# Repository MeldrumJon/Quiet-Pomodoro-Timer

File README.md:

# Visual-Timer

Shows timer progress on screen.  Flashes a bright LED when the timer expires 
instead of ringing or vibrating.  Useful for time management in quiet offices 
or libraries.

## Parts

- [16x2 Reflective LCD Character Display](https://www.mouser.com/ProductDetail/668-S16204XRGHS10B)
- ATMega328p-PU
    - With fuses set to use internal 8MHz clock (use Makefile: `make fuses`)
- [Rotary encoder with push button switch](https://www.mouser.com/ProductDetail/652-PEC11R4315KS0012)
- 2x [Bright LEDs](https://www.mouser.com/ProductDetail/78-TLHK46Q1R2)
- 10uF electrolytic capacitor
- 3x 0.1uF ceramic capacitors
- 2x 220 ohm resistors
- 10k ohm potentiometer
- Breakaway headers
- Battery holder for 3xAA or 3xAAA batteries

## Tools

- AVR ISP Programmer or [arduinoISP](https://www.arduino.cc/en/tutorial/arduinoISP)
- USB to TTY serial adapter for debugging.

## Schematic

## Setup

1. Install the AVR-GCC toolchain (and update your `PATH` variable, if necessary)
2. Connect the AVR ISP programmer pins to the ISP header on the PCB.
3. Connect the ATMega328p's TX pin to RX on the TTY serial adapter (optional)
4. Update the `program` and `fuses` recipes in the makefile to use your AVR 
ISP programmer.
5. Update the `serial` recipe in the makefile to use your USB to TTY serial 
adapter.
6. Run `make fuses` to set the fuses on the ATMega328p.
    - If the ATMega328p was previously set to use an external clock or crystal 
    oscillator, an external clock or crystal oscillator will be needed to set 
    the fuses.

## Programming

Run `make program` to program the ATMega328p.

## PCB

KiCAD files are in [the `hardware` Folder](./hardware).

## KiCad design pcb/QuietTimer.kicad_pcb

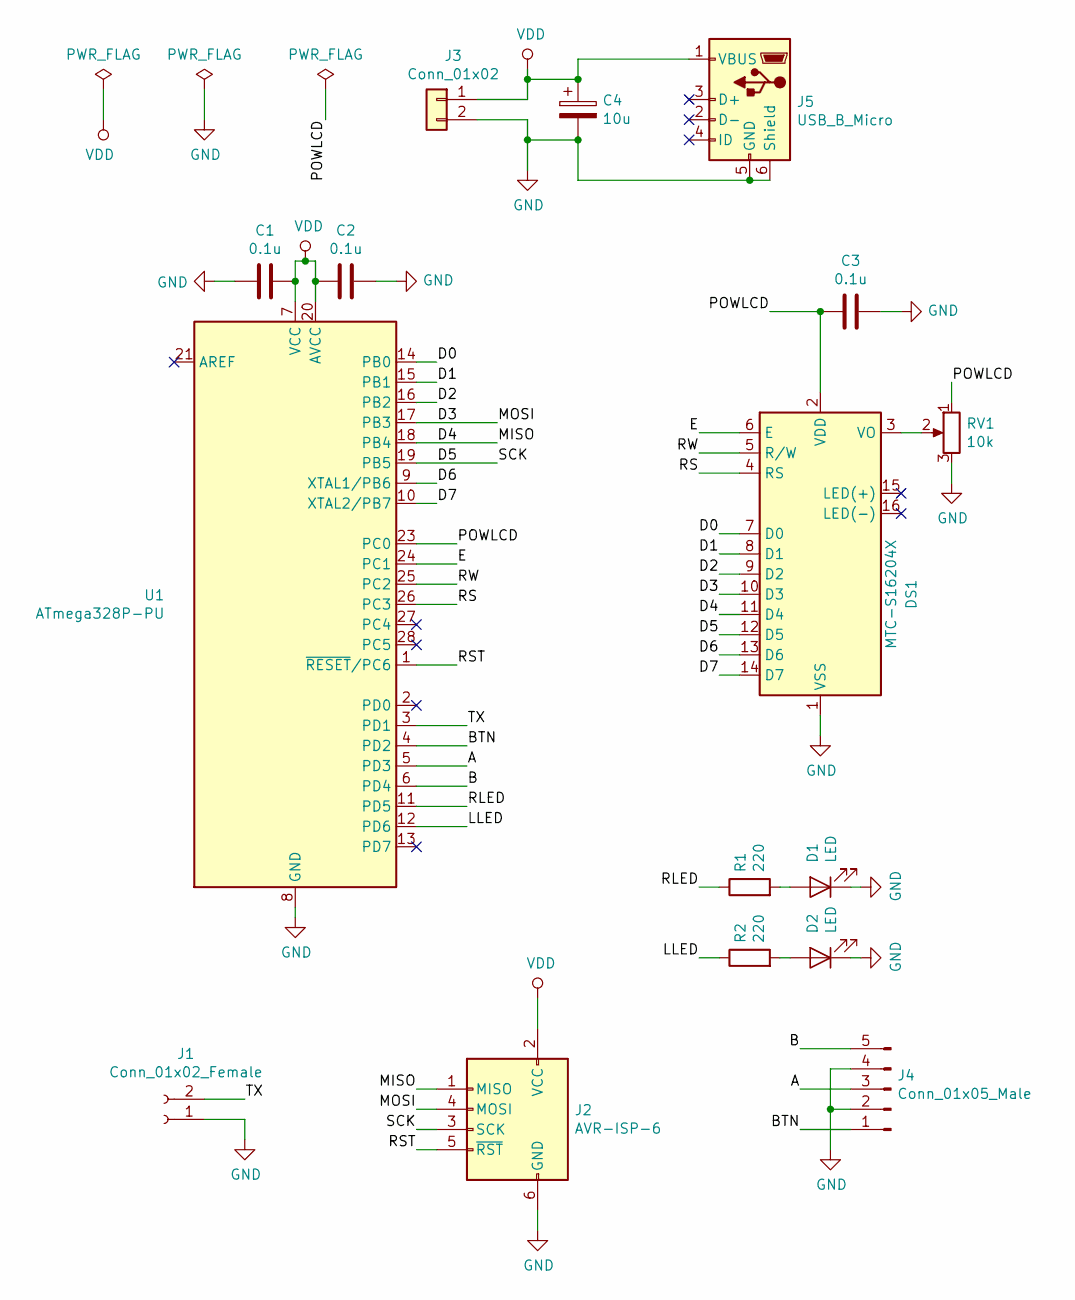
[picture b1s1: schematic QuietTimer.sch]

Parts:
C1, C2, C3: 0.1u; C_Disc_D5.0mm_W2.5mm_P2.50mm
C4: 10u; CP_Radial_D5.0mm_P2.00mm
D1, D2: LED; LED_D3.0mm
DS1: MTC-S16204X; MTC-16204X
J1: Conn_01x02_Female; PinSocket_1x02_P2.54mm_Vertical
J2: AVR-ISP-6; IDC-Header_2x03_P2.54mm_Vertical
J3: Conn_01x02; SolderWirePad_1x02_P3.81mm_Drill0.8mm
J4: Conn_01x05_Male; PinHeader_1x05_P2.54mm_Vertical
J5: USB_B_Micro; USB_Micro-B_Wuerth_614105150721_Vertical
R1, R2: 220; R_Axial_DIN0207_L6.3mm_D2.5mm_P2.54mm_Vertical
RV1: 10k; Potentiometer_Piher_PT-6-V_Vertical_Hole
U1: ATmega328P-PU; DIP-28_W7.62mm

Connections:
/A: J4.3, U1.5 (PD3)
/B: J4.5, U1.6 (PD4)
/BTN: J4.1, U1.4 (PD2)
/D0: DS1.7 (D0), U1.14 (PB0)
/D1: DS1.8 (D1), U1.15 (PB1)
/D2: DS1.9 (D2), U1.16 (PB2)
/D3: DS1.10 (D3), J2.4 (MOSI), U1.17 (PB3)
/D4: DS1.11 (D4), J2.1 (MISO), U1.18 (PB4)
/D5: DS1.12 (D5), J2.3 (SCK), U1.19 (PB5)
/D6: DS1.13 (D6), U1.9 (XTAL1/PB6)
/D7: DS1.14 (D7), U1.10 (XTAL2/PB7)
/E: DS1.6 (E), U1.24 (PC1)
/LLED: R2.1, U1.12 (PD6)
/POWLCD: C3.2, DS1.2 (VDD), RV1.1, U1.23 (PC0)
/RLED: R1.1, U1.11 (PD5)
/RS: DS1.4 (RS), U1.26 (PC3)
/RST: J2.5 (~RST), U1.1 (~RESET~/PC6)
/RW: DS1.5 (R/W), U1.25 (PC2)
/TX: J1.2, U1.3 (PD1)
GND: C1.2, C2.1, C3.1, C4.2, D1.1 (K), D2.1 (K), DS1.1 (VSS), J1.1, J2.6 (GND), J3.2, J4.2, J4.4, J5.5 (GND), J5.6 (Shield), RV1.3, U1.8 (GND), U1.22 (GND)
unnamed: D1.2 (A), R1.2
unnamed: D2.2 (A), R2.2
unnamed: DS1.3 (VO), RV1.2
VDD: C1.1, C2.2, C4.1, J2.2 (VCC), J3.1, J5.1 (VBUS), U1.7 (VCC), U1.20 (AVCC)

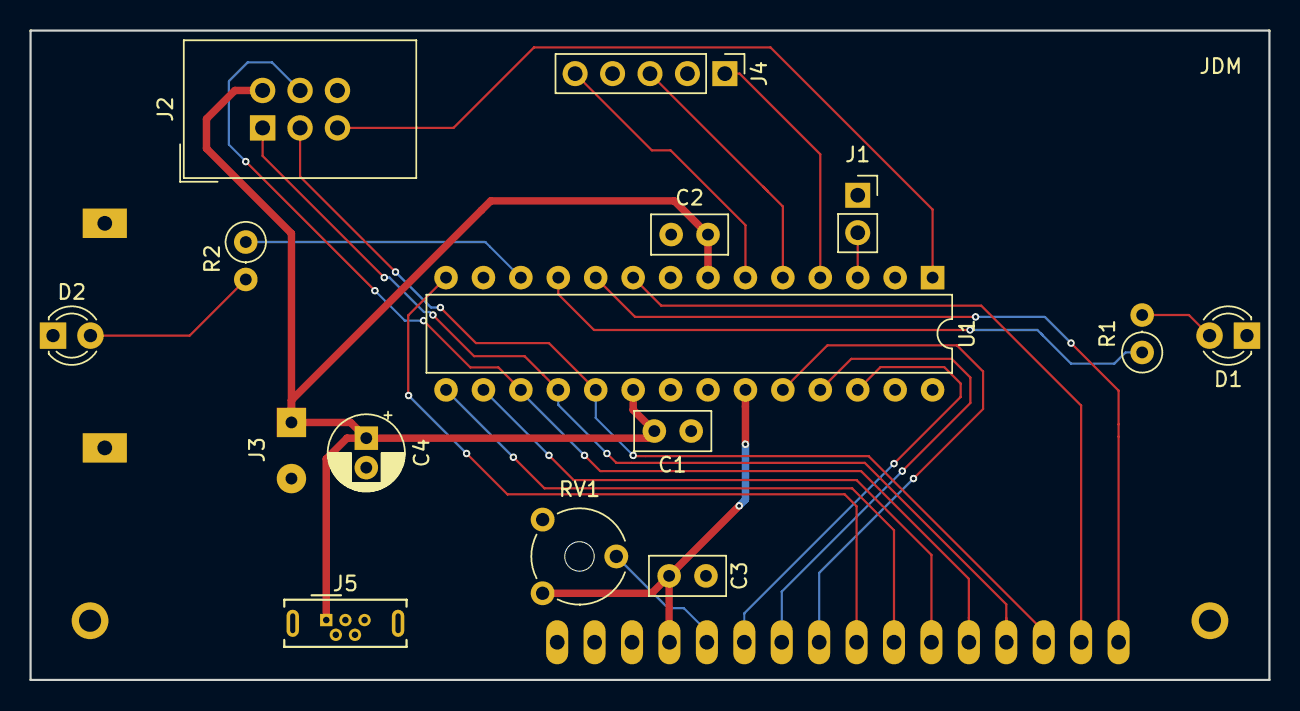
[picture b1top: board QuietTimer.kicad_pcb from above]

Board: 2 copper layers, 84.1 x 44.1 mm, 16 parts (1 on the bottom side), 24 nets.

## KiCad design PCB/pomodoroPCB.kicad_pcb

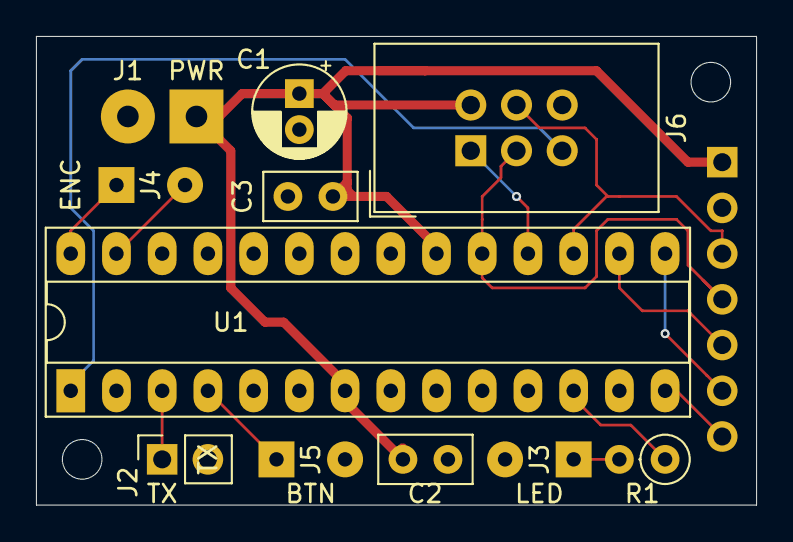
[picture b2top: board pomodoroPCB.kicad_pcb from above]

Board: 2 copper layers, 40.0 x 26.0 mm, 12 parts (1 on the bottom side), 15 nets.

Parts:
C1: 10u; CP_Radial_D5.0mm_P2.00mm
C2, C3: 0.1u; C_Disc_D5.0mm_W2.5mm_P2.50mm
J1: Conn_01x02; SolderWirePad_1x02_P3.81mm_Drill1.2mm
J2: Conn_01x02_Female; PinSocket_1x02_P2.54mm_Vertical
J3, J4, J5: Conn_01x02; SolderWirePad_1x02_P3.81mm_Drill0.8mm
J6: AVR-ISP-6; IDC-Header_2x03_P2.54mm_Vertical
J7: OLED_CONN; PinHeader_1x07_P2.54mm_Vertical
R1: 330; R_Axial_DIN0207_L6.3mm_D2.5mm_P2.54mm_Vertical
U1: ATmega328P-PU; DIP-28_W7.62mm_Socket_LongPads

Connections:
/TX: J2.1, U1.3
GND: C1.2, C2.2, C3.1, J1.2, J2.2, J3.2, J5.2, J6.6, J7.2, U1.8, U1.22
unnamed: J3.1, R1.2
unnamed: J4.1, U1.28
unnamed: J4.2, U1.27
unnamed: J5.1, U1.4
unnamed: J6.1, U1.18
unnamed: J6.3, J7.4, U1.19
unnamed: J6.4, J7.3, U1.17
unnamed: J6.5, U1.1
unnamed: J7.5, U1.16
unnamed: J7.6, U1.15
unnamed: J7.7, U1.14
unnamed: R1.1, U1.12
VCC: C1.1, C2.1, C3.2, J1.1, J6.2, J7.1, U1.7, U1.20

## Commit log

2018-07-26 Commit what I have so far.
2018-07-26 Comment on differences in .release
2018-07-27 Testing commits from VSCode
2018-07-27 Completed buttonFSM
2018-07-29 Added timerFSM
2018-08-01 Timer functionality
2018-08-02 Added Lights!
2018-08-03 Adjust brightness and resolution
2018-08-21 Added gamma LUT for better looking fades and brightness adjustment.
2018-08-27 Experiments with Encoder library, updates.
2018-08-28 Prepare the Encoder
2018-08-30 Almost there
2018-08-31 Ability to re-calibrate timer
2018-10-07 Moved to vscode-arduino
    Moved from PlatformIO to Microsoft's Arduino extension (for better board support).
2018-10-22 Trying Function Pointer Method
2018-10-22 Revert "Trying Function Pointer Method"
    This reverts commit 851c153de84a9b8ed708d1849c8ebfc863b1e4e3.
2019-01-03 Encoder, USART, WDT working
2019-01-04 Documentation
2019-05-26 Ignore build files
2019-05-26 Try manually setting power registers, use WDT
2019-06-16 Trying to compile arduino-core as library
2019-06-17 Compile core and run program
2019-06-18 Draw image on the screen
2019-06-18 Rudimentary Timer
2019-06-21 Low power working on TFT
    But I probably wont pursue a low power TFT display, it just draws too much current, still!
2019-06-25 OLED Test
2019-06-25 Drawing and Display Sleep
2019-06-26 Basic Power Saving, Fuse Settings
2019-06-28 All necessary IO working
2019-06-28 Refactor flags
2019-06-30 Almost Done
    TODO: low battery notification, don't flash the number when pressing start.
2019-06-30 Improvements
    Bugfix, power off on long button press, better transition to countdown.
2019-06-30 Cleanup
2019-07-24 LEDs, Code Cleanup
2019-08-16 Shorter LED blink time.
2019-09-11 PCB v0.1
2019-09-13 Add setup and programming instructions
2019-09-13 Add images
2019-09-13 Finish parts list
2019-09-13 Update Repo Name
2019-10-22 Move code, PCB into separate folders
2019-11-15 Switch from Female to Male Headers on PCB
2019-11-15 Beginning Enclosure
2019-12-01 3D Enclosure Refactor
2020-02-09 Enclosure changes
2020-02-09 Beginning of PCB
2020-02-10 Finish Custom Footprints
2020-02-10 Finished Schematic
2020-02-11 Finished PCB
2020-02-11 Reorganize
2020-03-02 LCD Control
2020-03-11 Character LCD Version Finished
2020-03-12 New Images
2020-03-16 Optimize LCD Write, Add Calibration
